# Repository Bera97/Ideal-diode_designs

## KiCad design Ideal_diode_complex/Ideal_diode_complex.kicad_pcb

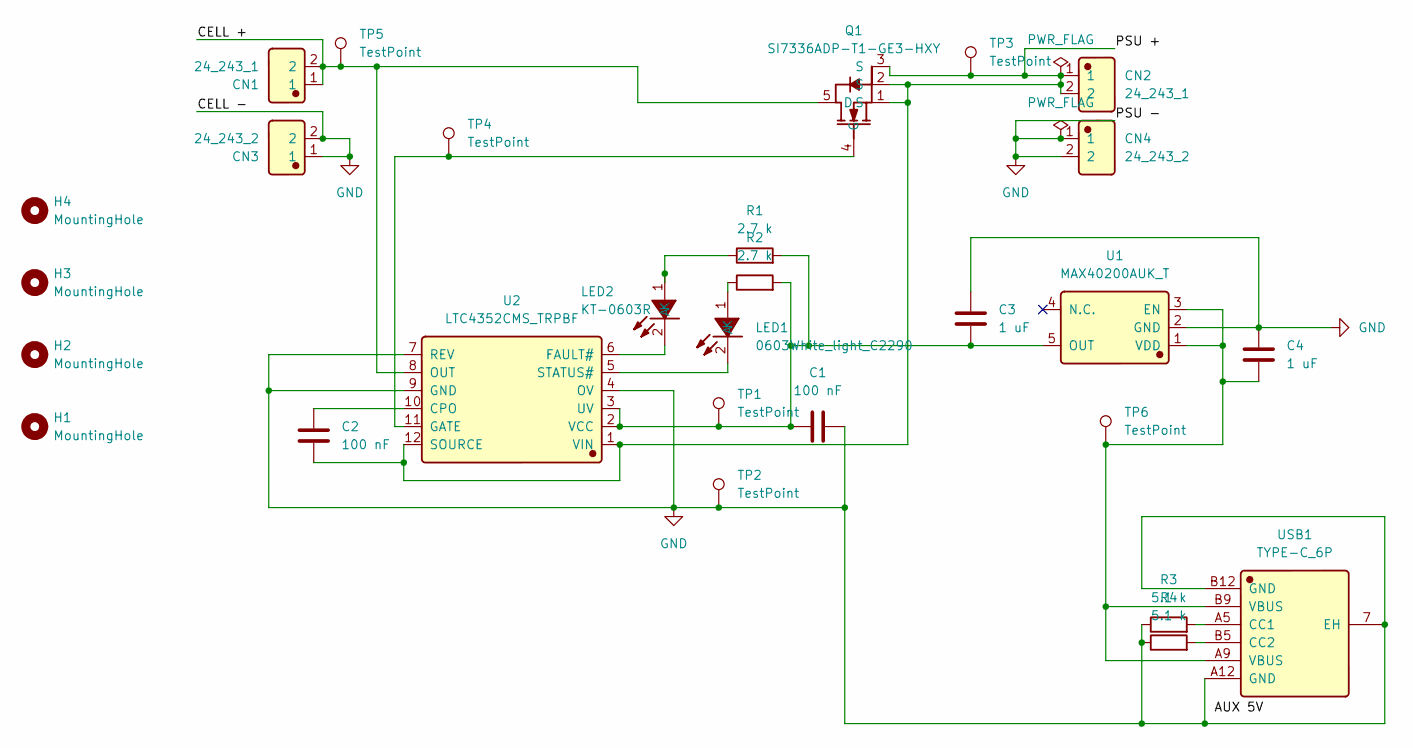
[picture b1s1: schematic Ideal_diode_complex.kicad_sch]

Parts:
C1, C2: 100 nF; C_0402_1005Metric
C3, C4: 1 uF; C_0402_1005Metric
CN1, CN2: 24_243_1; Manufacturer Part 24.243.1; LCSC C7437321
CN3, CN4: 24_243_2; Manufacturer Part 24.243.2; LCSC C7437322
H1, H2, H3, H4: MountingHole; MountingHole_2.7mm_M2.5
LED1: 0603White_light_C2290; Manufacturer Part KT-0603W; LCSC C2290
LED2: KT-0603R; Manufacturer Part KT-0603R; LCSC C2286
Q1: SI7336ADP-T1-GE3-HXY; Manufacturer Part SI7336ADP-T1-GE3-HXY; LCSC C22366654
R1, R2: 2.7 k; R_0603_1608Metric
R3, R4: 5.1 k; R_0402_1005Metric
TP1, TP2, TP3, TP4, TP5, TP6: TestPoint; TestPoint_Pad_D1.0mm
U1: MAX40200AUK_T; Manufacturer Part MAX40200AUK+T; LCSC C2649430
U2: LTC4352CMS_TRPBF; Manufacturer Part LTC4352CMS#TRPBF; LCSC C688177
USB1: TYPE-C_6P; Manufacturer Part TYPE-C 6P; LCSC C456012

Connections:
/CELL +: CN1.1, CN1.2, Q1.5 (D), TP5.1 (1_1), U2.8 (OUT)
/PSU +: C2.2, CN2.1, CN2.2, Q1.1 (S), Q1.2 (S), Q1.3 (S), TP3.1 (1_1), U2.1 (VIN), U2.12 (SOURCE)
GND: C1.2, C3.1, C4.1, CN3.1, CN3.2, CN4.1, CN4.2, R3.1, R4.1, TP2.1 (1_1), U1.2 (GND), U2.4 (OV), U2.7 (REV), U2.9 (GND), USB1.7 (EH), USB1.A12 (GND), USB1.B12 (GND)
unnamed: LED1.1 (A), R2.1
unnamed: LED1.2 (K), U2.5 (STATUS#)
unnamed: LED2.1 (A), R1.1
unnamed: LED2.2 (K), U2.6 (FAULT#)
unnamed: Q1.4 (G), TP4.1 (1_1), U2.11 (GATE)
unnamed: C4.2, TP6.1 (1_1), U1.1 (VDD), U1.3 (EN), USB1.A9 (VBUS), USB1.B9 (VBUS)
unnamed: C1.1, C3.2, R1.2, R2.2, TP1.1 (1_1), U1.5 (OUT), U2.2 (VCC), U2.3 (UV)
unnamed: C2.1, U2.10 (CPO)
unnamed: R3.2, USB1.A5 (CC1)
unnamed: R4.2, USB1.B5 (CC2)

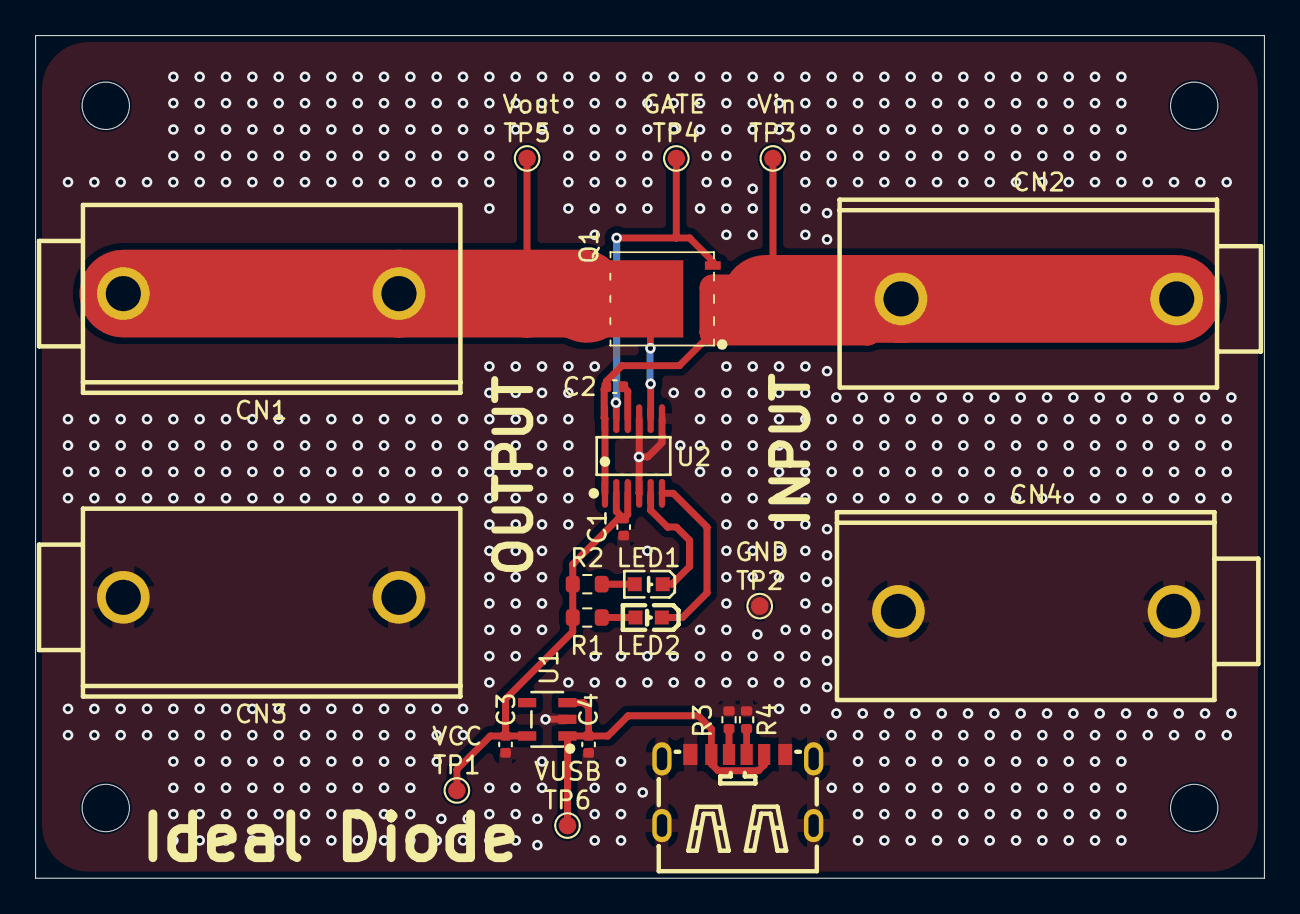
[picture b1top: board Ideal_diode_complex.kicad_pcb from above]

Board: 2 copper layers, 70.0 x 48.0 mm, 28 parts (0 on the bottom side), 13 nets.

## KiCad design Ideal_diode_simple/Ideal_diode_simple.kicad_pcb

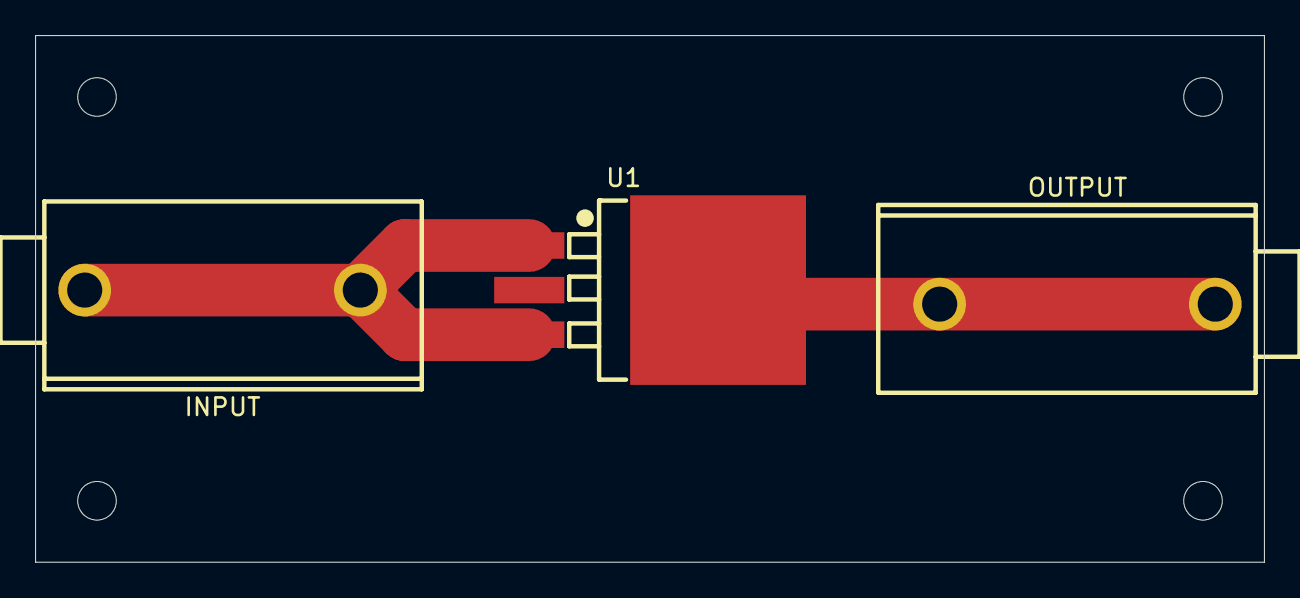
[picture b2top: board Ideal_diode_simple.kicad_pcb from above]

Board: 2 copper layers, 70.0 x 30.0 mm, 7 parts (0 on the bottom side), 2 nets.

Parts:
H1, H2, H3, H4: MountingHole; MountingHole_2.2mm_M2
INPUT: 24_243_1; Banana_plug_24_243_1
OUTPUT: 24_243_1; Banana_plug_24_243_1
U1: SM74611KTTR

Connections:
/V_in: INPUT.1, INPUT.2, U1.1 (ANODE), U1.3 (ANODE)
/V_out: OUTPUT.1, OUTPUT.2, U1.4 (CATHODE)

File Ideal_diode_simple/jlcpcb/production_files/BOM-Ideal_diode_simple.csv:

Comment,Designator,Footprint,LCSC,Quantity
24_243_1,"INPUT,OUTPUT",Banana_plug_24_243_1,C7437321,2
SM74611KTTR,U1,SM74611KTTR,C181638,1

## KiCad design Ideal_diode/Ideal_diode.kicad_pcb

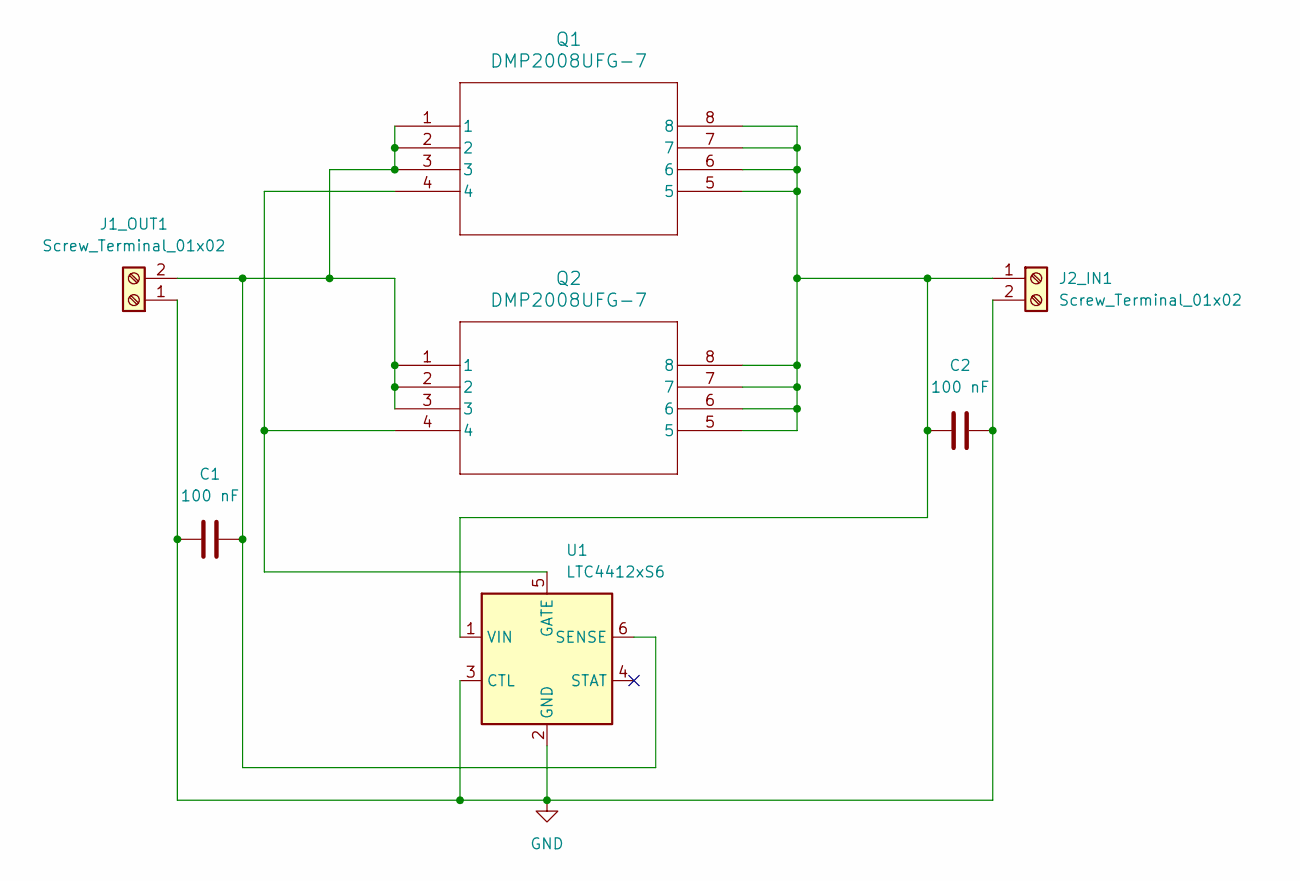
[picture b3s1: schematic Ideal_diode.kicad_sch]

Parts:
C1, C2: 100 nF; C_0805_2012Metric
J1_OUT1, J2_IN1: Screw_Terminal_01x02; TerminalBlock_Phoenix_MKDS-1,5-2_1x02_P5.00mm_Horizontal
Q1, Q2: DMP2008UFG-7; DMP2008UFG-7_DIO_fixed
U1: LTC4412xS6; TSOT-23-6

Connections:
GND: C1.1, C2.2, J1_OUT1.1, J2_IN1.2, U1.2 (GND), U1.3 (CTL)
unnamed: C1.2, J1_OUT1.2, Q1.1, Q1.2, Q1.3, Q2.1, Q2.2, Q2.3, U1.6 (SENSE)
unnamed: C2.1, J2_IN1.1, Q1.5, Q1.6, Q1.7, Q1.8, Q2.5, Q2.6, Q2.7, Q2.8, U1.1 (VIN)
unnamed: Q1.4, Q2.4, U1.5 (GATE)

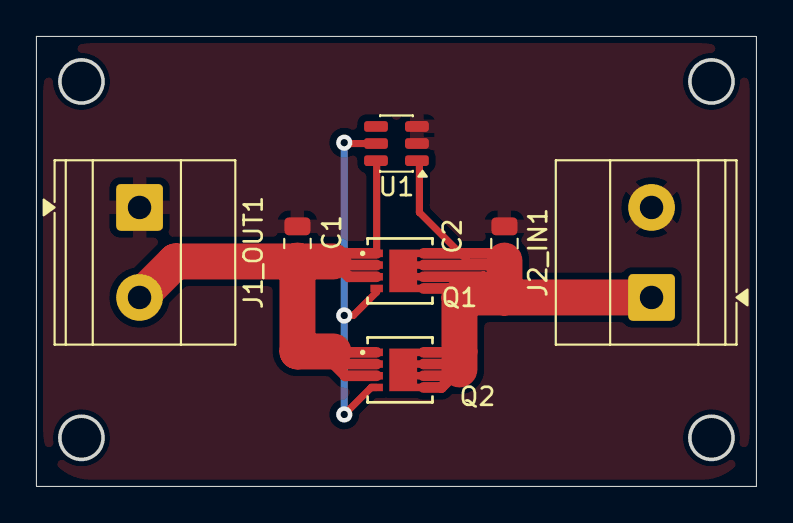
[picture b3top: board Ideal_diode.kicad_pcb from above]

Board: 2 copper layers, 40.0 x 25.0 mm, 7 parts (0 on the bottom side), 4 nets.
